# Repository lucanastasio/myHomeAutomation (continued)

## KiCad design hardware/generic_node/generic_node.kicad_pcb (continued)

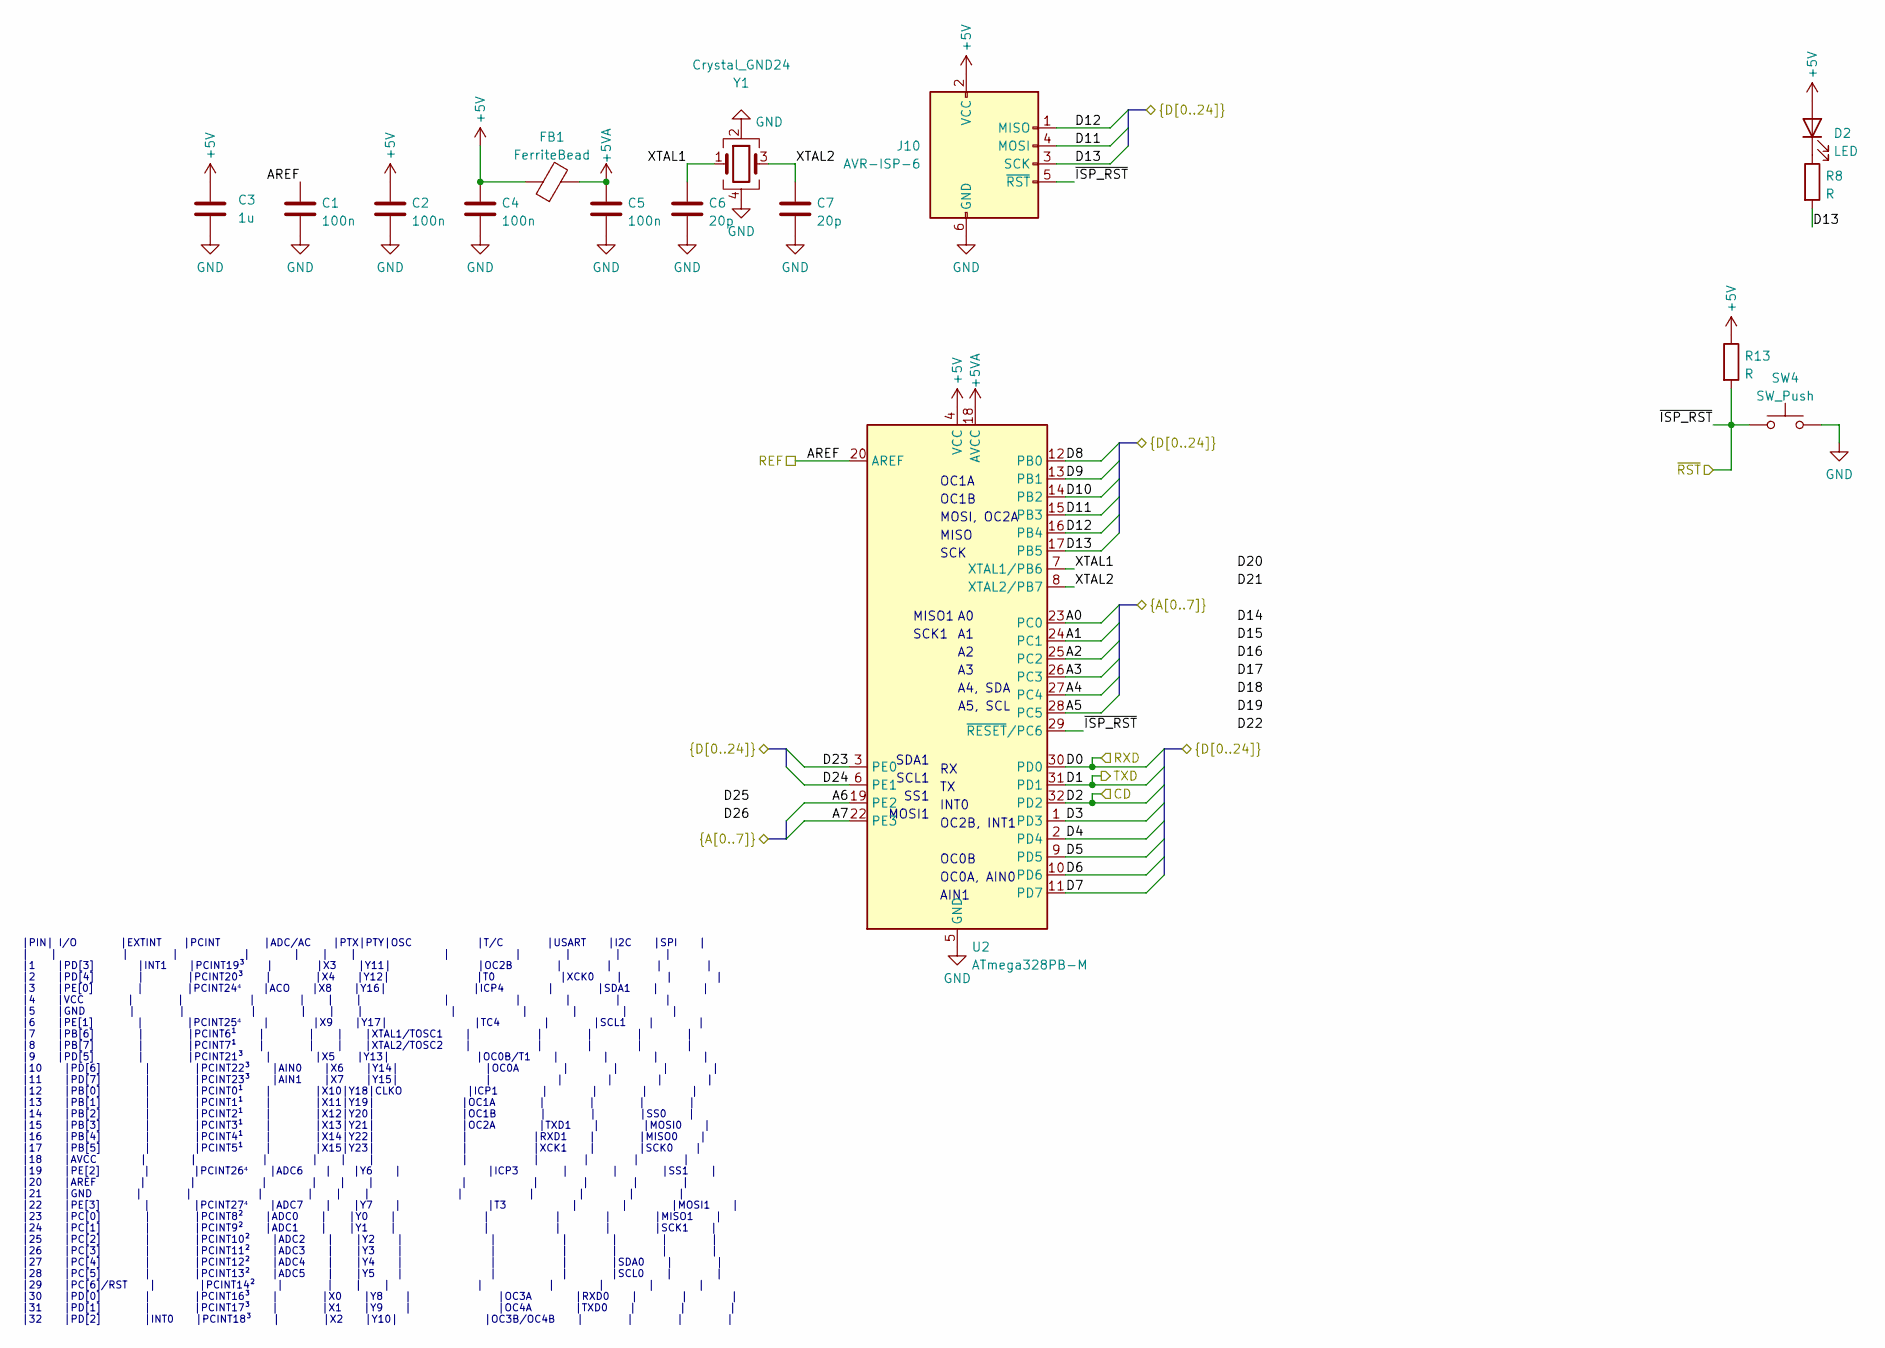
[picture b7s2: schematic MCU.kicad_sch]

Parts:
C1, C2, C4, C5: 100n; C_0402_1005Metric
C3: 1u; C_0402_1005Metric
C6, C7: 20p; C_0402_1005Metric
D2: LED; LED_0402_1005Metric
FB1: FerriteBead; L_0402_1005Metric
J10: AVR-ISP-6; PinHeader_2x03_P2.54mm_Vertical
R8, R13: R; R_0402_1005Metric
SW4: SW_Push; SW_SPST_B3U-1000P
U2: ATmega328PB-M; QFN-32-1EP_5x5mm_P0.5mm_EP3.1x3.1mm
Y1: Crystal_GND24; Crystal_SMD_2520-4Pin_2.5x2.0mm

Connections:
+5V: C2.2, C3.2, C4.1, D2.2 (A), FB1.1, J10.2 (VCC), R13.1, U2.4 (VCC); also elsewhere on the board
+5VA: C5.1, FB1.2, U2.18 (AVCC)
/A0: U2.23 (PC0); also elsewhere on the board
/A1: U2.24 (PC1); also elsewhere on the board
/A2: U2.25 (PC2); also elsewhere on the board
/A3: U2.26 (PC3); also elsewhere on the board
/A4: U2.27 (PC4); also elsewhere on the board
/A5: U2.28 (PC5); also elsewhere on the board
/A6: U2.19 (PE2); also elsewhere on the board
/A7: U2.22 (PE3); also elsewhere on the board
/D0: U2.30 (PD0); also elsewhere on the board
/D1: U2.31 (PD1); also elsewhere on the board
/D2: U2.32 (PD2); also elsewhere on the board
/D3: U2.1 (PD3); also elsewhere on the board
/D4: U2.2 (PD4); also elsewhere on the board
/D5: U2.9 (PD5); also elsewhere on the board
/D6: U2.10 (PD6); also elsewhere on the board
/D7: U2.11 (PD7); also elsewhere on the board
/D8: U2.12 (PB0); also elsewhere on the board
/D9: U2.13 (PB1); also elsewhere on the board
/D10: U2.14 (PB2); also elsewhere on the board
/D11: J10.4 (MOSI), U2.15 (PB3); also elsewhere on the board
/D12: J10.1 (MISO), U2.16 (PB4); also elsewhere on the board
/D13: J10.3 (SCK), R8.2, U2.17 (PB5); also elsewhere on the board
/D23: U2.3 (PE0); also elsewhere on the board
/D24: U2.6 (PE1); also elsewhere on the board
/MCU/XTAL1: C6.1, U2.7 (XTAL1/PB6), Y1.1
/MCU/XTAL2: C7.1, U2.8 (XTAL2/PB7), Y1.3
/REF: C1.1, U2.20 (AREF); also elsewhere on the board
/~RST: J10.5 (~RST), R13.2, SW4.1, U2.29 (~RESET/PC6); also elsewhere on the board
GND: C1.2, C2.1, C3.1, C4.2, C5.2, C6.2, C7.2, J10.6 (GND), SW4.2, U2.5 (GND), U2.21 (GND), U2.33 (GND), Y1.2, Y1.4; also elsewhere on the board
unnamed: D2.1 (K), R8.1

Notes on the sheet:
OC0B
OC1B
SS1
OC1A
MISO
SCK1
|PIN| I/O |EXTINT |PCINT |ADC/AC |PTX|PTY|OSC |T/C |USART |I2C |SPI | | | | | | | | | | | | | | |1 |PD[3] |INT1 |PCINT19³ | |X3 |Y11| |OC2B | | | | |2 |PD[4] | |PCINT20³ | |X4 |Y12| |T0 |XCK0 | | | |3 |PE[0] | |PCINT24⁴ |ACO |X8 |Y16| |ICP4 | |SDA1 | | |4 |VCC | | | | | | | | | | | |5 |GND | | | | 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
SCL1
A4, SDA
OC2B, INT1
SDA1
INT0
OC0A, AIN0
MOSI, OC2A
SCK
MISO1
AIN1
A5, SCL
MOSI1

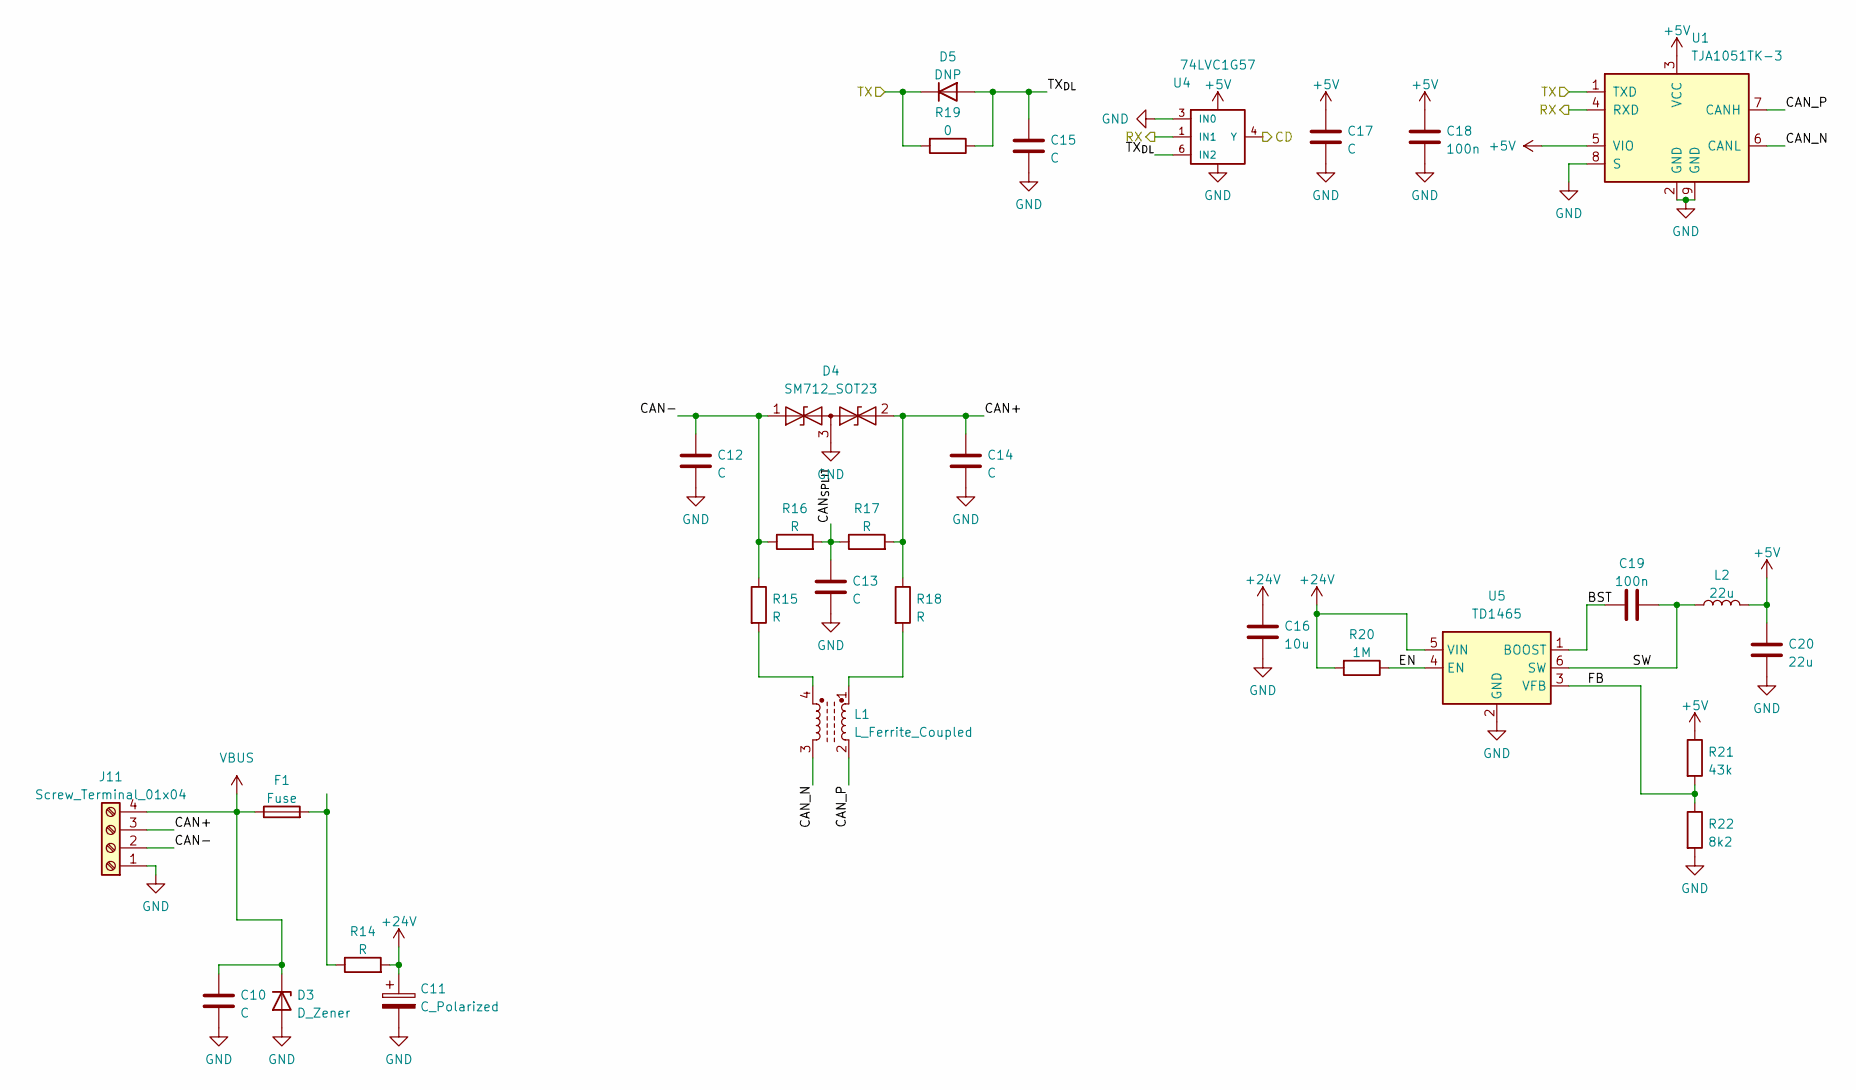
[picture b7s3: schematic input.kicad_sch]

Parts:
C10, C12, C14: C; C_0603_1608Metric
C11: C_Polarized; C_Disc_D3.0mm_W1.6mm_P2.50mm
C13: C; C_0805_2012Metric_Pad1.18x1.45mm_HandSolder
C15, C17: C; C_0402_1005Metric
C16: 10u; C_1206_3216Metric
C18, C19: 100n; C_0402_1005Metric
C20: 22u; C_0805_2012Metric
D3: D_Zener; D_SMA
D4: SM712_SOT23; SOT-23
D5: DNP; D_SOD-523
F1: Fuse; Fuse_0805_2012Metric_Pad1.15x1.40mm_HandSolder
J11: Screw_Terminal_01x04; PhoenixContact_MC_1,5_4-G-3.81_1x04_P3.81mm_Horizontal
L1: L_Ferrite_Coupled; L_CommonModeChoke_Coilcraft_0805USB
L2: 22u; L_1210_3225Metric
R14: R; R_0805_2012Metric
R15, R18: R; R_0603_1608Metric
R16, R17: R; R_0805_2012Metric_Pad1.20x1.40mm_HandSolder
R19: 0; R_0402_1005Metric
R20: 1M; R_0402_1005Metric
R21: 43k; R_0402_1005Metric
R22: 8k2; R_0402_1005Metric
U1: TJA1051TK-3; DFN-8-1EP_3x3mm_P0.65mm_EP1.55x2.4mm
U4: 74LVC1G57; SOT-563
U5: TD1465; SOT-23-6

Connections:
+5V: C17.1, C18.2, C20.2, L2.2, R21.1, U1.3 (VCC), U1.5 (VIO), U4.5 (VCC); also elsewhere on the board
+24V: C11.1, C16.2, R14.2, R20.2, U5.5 (VIN)
/D0: U1.4 (RXD), U4.1 (IN1); also elsewhere on the board
/D1: D5.1 (K), R19.2, U1.1 (TXD); also elsewhere on the board
/D2: U4.4 (Y); also elsewhere on the board
/input, power, bus/BST: C19.1, U5.1 (BOOST)
/input, power, bus/CAN+: C14.1, D4.2 (A2), J11.3, R17.2, R18.1
/input, power, bus/CAN-: C12.1, D4.1 (A1), J11.2, R15.1, R16.1
/input, power, bus/CAN_N: L1.3, U1.6 (CANL)
/input, power, bus/CAN_P: L1.2, U1.7 (CANH)
/input, power, bus/CAN_{SPLIT}: C13.1, R16.2, R17.1
/input, power, bus/EN: R20.1, U5.4 (EN)
/input, power, bus/FB: R21.2, R22.1, U5.3 (VFB)
/input, power, bus/SW: C19.2, L2.1, U5.6 (SW)
/input, power, bus/TX_{DL}: C15.1, D5.2 (A), R19.1, U4.6 (IN2)
GND: C10.2, C11.2, C12.2, C13.2, C14.2, C15.2, C16.1, C17.2, C18.1, C20.1, D3.2 (A), D4.3 (common), J11.1, R22.2, U1.2 (GND), U1.8 (S), U1.9 (GND), U4.2 (GND), U4.3 (IN0), U5.2 (GND); also elsewhere on the board
unnamed: F1.2, R14.1
unnamed: L1.1, R18.2
unnamed: L1.4, R15.2
VBUS: C10.1, D3.1 (K), F1.1, J11.4; also elsewhere on the board

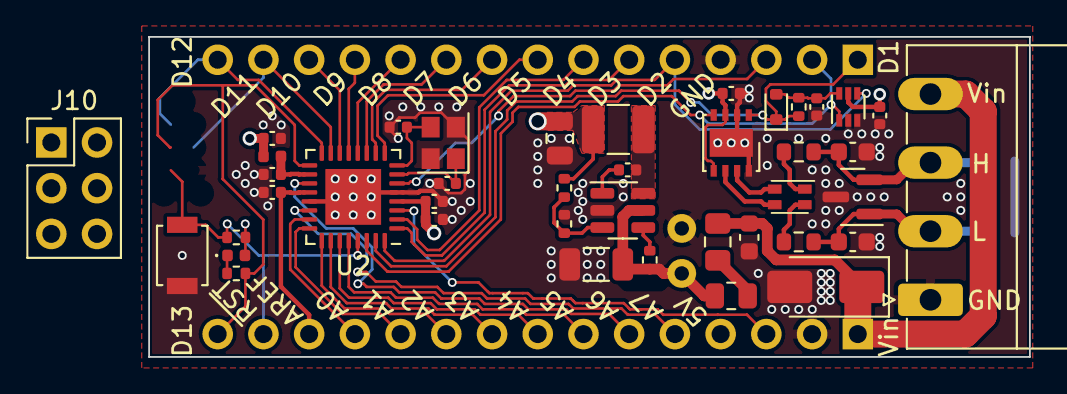
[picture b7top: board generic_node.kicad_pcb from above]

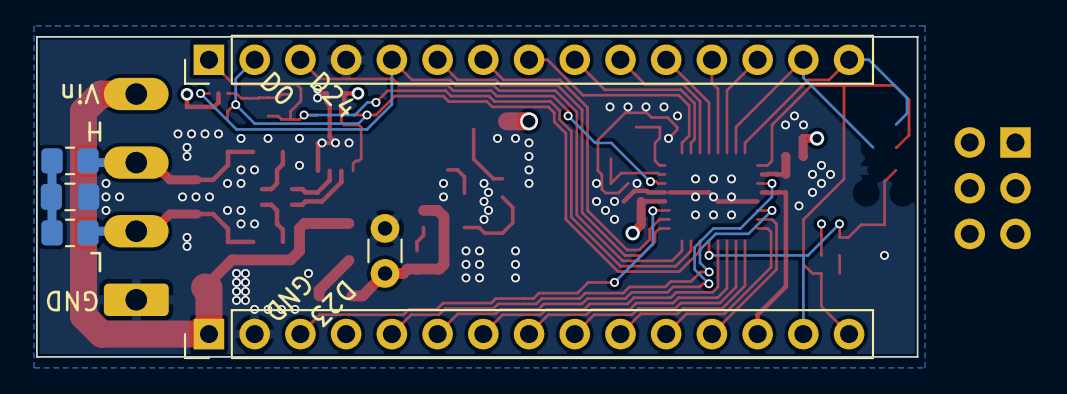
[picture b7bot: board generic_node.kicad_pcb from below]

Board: 4 copper layers, 48.9 x 17.8 mm, 47 parts (6 on the bottom side), 47 nets.

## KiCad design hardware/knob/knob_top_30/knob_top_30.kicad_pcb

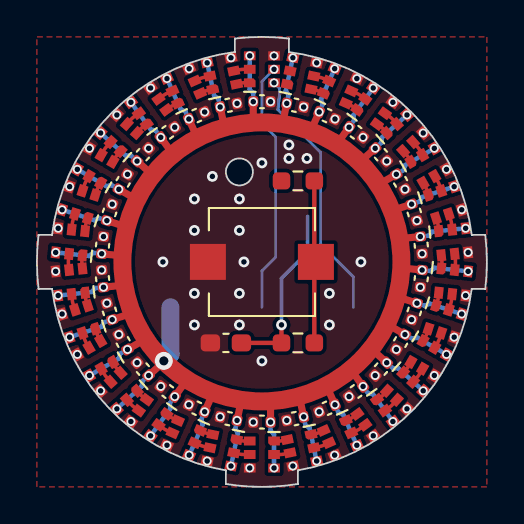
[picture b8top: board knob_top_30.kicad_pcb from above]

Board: 2 copper layers, 25.0 x 25.0 mm, 65 parts (1 on the bottom side), 64 nets.

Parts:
C1, C2, C3, C4, C5, C6, C7, C8, C9, C10, C11, C12, C13, C14, C15, C16, C17, C18, C19, C20, C21, C22, C23, C24, C25, C26, C27, C28, C29, C30: 100n; C_0402_1005Metric
C31: C; C_0603_1608Metric_Pad1.08x0.95mm_HandSolder
D1, D2, D3, D4, D5, D6, D7, D8, D9, D10, D11, D12, D13, D14, D15, D16, D17, D18, D19, D20, D21, D22, D23, D24, D25, D26, D27, D28, D29, D30: APA102-2020; LED-HD107S-2020
J1: Conn_02x05_Odd_Even; PinHeader_2x05_P2.54mm_Vertical_SMD
R1, R2: R; R_0603_1608Metric_Pad0.98x0.95mm_HandSolder
SW1: SW_Push; SKPSACE010

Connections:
+5V: C1.1, C2.1, C3.1, C4.1, C5.1, C6.1, C7.1, C8.1, C9.1, C10.1, C11.1, C12.1, C13.1, C14.1, C15.1, C16.1, C17.1, C18.1, C19.1, C20.1, C21.1, C22.1, C23.1, C24.1, C25.1, C26.1, C27.1, C28.1, C29.1, C30.1, D1.1 (VDD), D2.1 (VDD), D3.1 (VDD), D4.1 (VDD), D5.1 (VDD), D6.1 (VDD), D7.1 (VDD), D8.1 (VDD), D9.1 (VDD), D10.1 (VDD), D11.1 (VDD), D12.1 (VDD), D13.1 (VDD), D14.1 (VDD), D15.1 (VDD), D16.1 (VDD), D17.1 (VDD), D18.1 (VDD), D19.1 (VDD), D20.1 (VDD), D21.1 (VDD), D22.1 (VDD), D23.1 (VDD), D24.1 (VDD), D25.1 (VDD), D26.1 (VDD), D27.1 (VDD), D28.1 (VDD), D29.1 (VDD), D30.1 (VDD), J1.2, R1.1
/MOSI: D1.4 (SDI), J1.10
/PB: C31.1, J1.7, R2.2
/SCK: D1.5 (CKI), J1.6
GND: C1.2, C2.2, C3.2, C4.2, C5.2, C6.2, C7.2, C8.2, C9.2, C10.2, C11.2, C12.2, C13.2, C14.2, C15.2, C16.2, C17.2, C18.2, C19.2, C20.2, C21.2, C22.2, C23.2, C24.2, C25.2, C26.2, C27.2, C28.2, C29.2, C30.2, C31.2, D1.6 (GND), D2.6 (GND), D3.6 (GND), D4.6 (GND), D5.6 (GND), D6.6 (GND), D7.6 (GND), D8.6 (GND), D9.6 (GND), D10.6 (GND), D11.6 (GND), D12.6 (GND), D13.6 (GND), D14.6 (GND), D15.6 (GND), D16.6 (GND), D17.6 (GND), D18.6 (GND), D19.6 (GND), D20.6 (GND), D21.6 (GND), D22.6 (GND), D23.6 (GND), D24.6 (GND), D25.6 (GND), D26.6 (GND), D27.6 (GND), D28.6 (GND), D29.6 (GND), D30.6 (GND), J1.1, J1.9, SW1.1
unnamed: D1.2 (CKO), D2.5 (CKI)
unnamed: D1.3 (SDO), D2.4 (SDI)
unnamed: D2.2 (CKO), D3.5 (CKI)
unnamed: D2.3 (SDO), D3.4 (SDI)
unnamed: D3.2 (CKO), D4.5 (CKI)
unnamed: D3.3 (SDO), D4.4 (SDI)
unnamed: D4.2 (CKO), D5.5 (CKI)
unnamed: D4.3 (SDO), D5.4 (SDI)
unnamed: D5.2 (CKO), D6.5 (CKI)
unnamed: D5.3 (SDO), D6.4 (SDI)
unnamed: D6.2 (CKO), D7.5 (CKI)
unnamed: D6.3 (SDO), D7.4 (SDI)
unnamed: D7.2 (CKO), D8.5 (CKI)
unnamed: D7.3 (SDO), D8.4 (SDI)
unnamed: D8.2 (CKO), D9.5 (CKI)
unnamed: D8.3 (SDO), D9.4 (SDI)
unnamed: D9.2 (CKO), D10.5 (CKI)
unnamed: D10.2 (CKO), D11.5 (CKI)
unnamed: D9.3 (SDO), D10.4 (SDI)
unnamed: D10.3 (SDO), D11.4 (SDI)
unnamed: D11.2 (CKO), D12.5 (CKI)
unnamed: D11.3 (SDO), D12.4 (SDI)
unnamed: D12.2 (CKO), D13.5 (CKI)
unnamed: D12.3 (SDO), D13.4 (SDI)
unnamed: D13.2 (CKO), D14.5 (CKI)
unnamed: D13.3 (SDO), D14.4 (SDI)
unnamed: D14.2 (CKO), D15.5 (CKI)
unnamed: D14.3 (SDO), D15.4 (SDI)
unnamed: D15.2 (CKO), D16.5 (CKI)
unnamed: D15.3 (SDO), D16.4 (SDI)
unnamed: D16.2 (CKO), D17.5 (CKI)
unnamed: D16.3 (SDO), D17.4 (SDI)
unnamed: D17.2 (CKO), D18.5 (CKI)
unnamed: D17.3 (SDO), D18.4 (SDI)
unnamed: D18.2 (CKO), D19.5 (CKI)
unnamed: D18.3 (SDO), D19.4 (SDI)
unnamed: D19.2 (CKO), D20.5 (CKI)
unnamed: D19.3 (SDO), D20.4 (SDI)
unnamed: D20.2 (CKO), D21.5 (CKI)
unnamed: D20.3 (SDO), D21.4 (SDI)
unnamed: D21.2 (CKO), D22.5 (CKI)
unnamed: D21.3 (SDO), D22.4 (SDI)
unnamed: D22.2 (CKO), D23.5 (CKI)
unnamed: D22.3 (SDO), D23.4 (SDI)
unnamed: D23.2 (CKO), D24.5 (CKI)
unnamed: D23.3 (SDO), D24.4 (SDI)
unnamed: D24.2 (CKO), D25.5 (CKI)
unnamed: D24.3 (SDO), D25.4 (SDI)
unnamed: D25.2 (CKO), D26.5 (CKI)
unnamed: D25.3 (SDO), D26.4 (SDI)
unnamed: D26.2 (CKO), D27.5 (CKI)
unnamed: D26.3 (SDO), D27.4 (SDI)
unnamed: D27.2 (CKO), D28.5 (CKI)
unnamed: D27.3 (SDO), D28.4 (SDI)
unnamed: D28.2 (CKO), D29.5 (CKI)
unnamed: D28.3 (SDO), D29.4 (SDI)
unnamed: D29.2 (CKO), D30.5 (CKI)
unnamed: D29.3 (SDO), D30.4 (SDI)
unnamed: R1.2, R2.1, SW1.2

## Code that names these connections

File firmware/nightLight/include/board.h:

/* Copyright (c) 2024 Luca Anastasio
 *
 * Board definitions
 *
 */

#ifndef BOARD_H
#define BOARD_H

#include <Arduino.h>
#include "wiring_private.h"

/* Pins
 * IO	Peripheral	Usage			Active level
 * PB0	OC0A		LED				High
 * PB1	IN			PIR				High
 * PB2	ADC1?		Vsense			*Low
 * PB3	ADC3		Ambient light	*Low
 * PB4	IN			User button		Low
 */

// NOTE: Suggested LED PWM frequency = 20kHz to 100kHz

#define ADC_BITS 10

#ifdef __AVR_ATmega328P__

#include <Debounce.h>

#define millis_t uint16_t

#define LED_PIN 13
// #define LED_PWM
#define PIR_PIN 11
#define VSN_PIN A1
#define ALS_PIN A3
#define BTN_PIN 12
#define VSN_ADC 1
#define ALS_ADC 3

#define ADC_PRESCALER 7 // prescale 16MHz by 128 -> 125kHz ADC clock
#define ADC_REFERENCE 0 // Vcc as reference

#define SET_LED(x) digitalWrite(LED_PIN, x)
#define PIR_DETECT() digitalRead(PIR_PIN)
#define USRBTN_PRESSED() !debouncedDigitalRead(BTN_PIN)
#define ADC_START() sbi(ADCSRA, ADSC)
#define ADC_COMPLETE() bit_is_clear(ADCSRA, ADSC)
#define ADC_MUX_SET(m) ADMUX = (ADC_REFERENCE << 6) | m
#define ADC_MUX_GET() (ADMUX & 0x03)

static inline void board_init()
{
	debouncePins(BTN_PIN, BTN_PIN);
	pinMode(LED_PIN, OUTPUT);
	pinMode(BTN_PIN, INPUT_PULLUP);
	ADC_MUX_SET(VSN_ADC); // set the ADC mux for the first conversion
	ADCSRA = _BV(ADEN) | _BV(ADSC) | ADC_PRESCALER;
}

#elif defined(__AVR_ATtiny13__)

#define millis_t uint16_t

#define LED_PIN PB0
#define LED_PWM OCR0A
#define PIR_PIN PB1
#define VSN_PIN PB2
#define ALS_PIN PB3
#define BTN_PIN PB4
#define VSN_ADC 1
#define ALS_ADC 3

#define ADC_PRESCALER 7 // prescale 9.6MHz by 128 -> 75kHz ADC clock
#define ADC_REFERENCE 0 // Vcc as reference

#define SET_LED(x) LED_PWM = x
#define PIR_DETECT() bit_is_set(PINB, PIR_PIN)
#define USRBTN_PRESSED() bit_is_clear(PINB, BTN_PIN)
#define ADC_START() sbi(ADCSRA, ADSC)
#define ADC_COMPLETE() bit_is_clear(ADCSRA, ADSC)
#define ADC_MUX_GET() (ADMUX & 0x03)
#if ADC_BITS == 8
	#define ADC_MUX_SET(m) ADMUX = (ADC_REFERENCE << 6) | _BV(ADLAR) | m
	#define ADC_VAL_GET() ADCH
	#define adc_t uint8_t
	#define ADC_VAL_INIT 0xFF
#else
	#define ADC_MUX_SET(m) ADMUX = (ADC_REFERENCE << 6) | m
	#define ADC_VAL_GET() ADCW
	#define adc_t uint16_t
	#define ADC_VAL_INIT 0xFFFF
#endif



static inline void board_init()
{
	sbi(DDRB, LED_PIN);						// set the LED pin as the only output
	DIDR0 = (_BV(ALS_ADC) | _BV(VSN_ADC)) << 2; // disable digital inputs for ADC channels
	ADC_MUX_SET(VSN_ADC);						// set the ADC mux for the first conversion
	ADCSRA = _BV(ADEN) | _BV(ADSC) | ADC_PRESCALER;
	TCCR0B = _BV(CS00); // 9.6MHz sys clock -> 9.6MHz timer clock -> 37.5kHz PWM frequency
	TCCR0A = _BV(WGM00) | _BV(WGM01) | _BV(COM0A1);
}

#endif

#endif // BOARD_H

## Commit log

2023-11-01 hw layout
2023-12-16 led balance and corridor ready
2023-12-17 night light ready
2023-12-22 adde schematics
2024-02-17 various
2024-12-08 working
2025-03-22 Night Light firmware
2025-06-21 updated night light firmware
2025-06-21 started corridor light controller firmware
2025-07-05 corridorController firmware update
2025-07-05 nightLight firmware minor correction
2025-07-05 nightLight pcb files version upgrade
2025-10-18 firmware input/output sections, main still in progress
2025-12-21 completed repeater
2026-01-18 started remote pcb
2026-01-18 mpcm example on generic node
